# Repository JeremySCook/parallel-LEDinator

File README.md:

# parallel-LEDinator
LED indicators for DB25 parallel connections

Video: https://www.youtube.com/watch?v=P86tV40nX3E

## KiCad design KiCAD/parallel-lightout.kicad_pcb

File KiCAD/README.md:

KiCAD files - newest version as of 5/6/2020

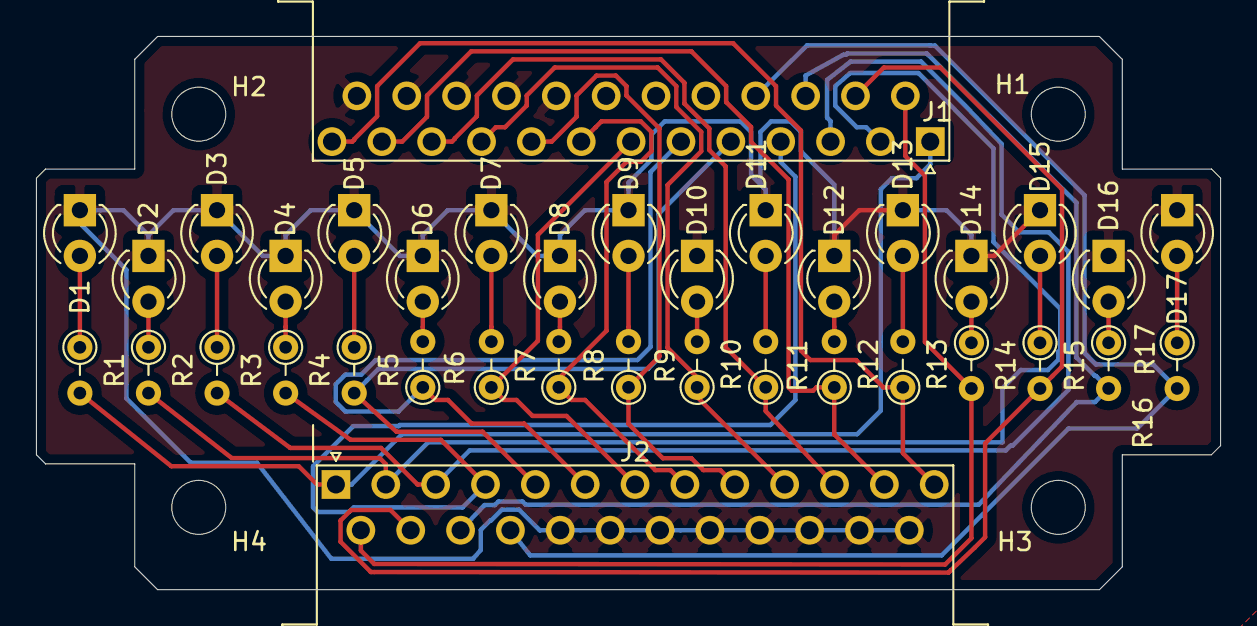
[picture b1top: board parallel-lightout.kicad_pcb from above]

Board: 2 copper layers, 65.8 x 30.7 mm, 40 parts (0 on the bottom side), 35 nets.

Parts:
D1, D2, D3, D4, D5, D6, D7, D8, D9, D10, D11, D12, D13, D14, D15, D16, D17: LED; LED_D3.0mm
H1, H2, H3, H4: MountingHole; MountingHole_3mm
J1, J2: DB25_Male; DSUB-25_Male_Horizontal_P2.77x2.54mm_EdgePinOffset9.40mm
R1, R2, R3, R4, R5, R6, R7, R8, R9, R10, R11, R12, R13, R14, R15, R16, R17: R; R_Axial_DIN0204_L3.6mm_D1.6mm_P2.54mm_Vertical

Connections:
/1: J1.1, J2.1, R1.2
/2: J1.2, J2.2, R2.2
/3: J1.3, J2.3, R3.2
/4: J1.4, J2.4, R4.2
/5: J1.5, J2.5, R5.2
/6: J1.6, J2.6, R6.1
/7: J1.7, J2.7, R7.1
/8: J1.8, J2.8, R8.1
/9: J1.9, J2.9, R9.1
/10: J1.10, J2.10, R10.1
/11: J1.11, J2.11, R11.1
/12: J1.12, J2.12, R12.1
/13: J1.13, J2.13, R13.1
/14: J1.14, J2.14, R14.2
/15: J1.15, J2.15, R15.2
/16: J1.16, J2.16, R16.2
/17: J1.17, J2.17, R17.2
GND: D1.1, D2.1, D3.1, D4.1, D5.1, D6.1, D7.1, D8.1, D9.1, D10.1, D11.1, D12.1, D13.1, D14.1, D15.1, D16.1, D17.1, J1.18, J1.19, J1.20, J1.21, J1.22, J1.23, J1.24, J1.25, J2.18, J2.19, J2.20, J2.21, J2.22, J2.23, J2.24, J2.25
unnamed: D1.2, R1.1
unnamed: D2.2, R2.1
unnamed: D3.2, R3.1
unnamed: D4.2, R4.1
unnamed: D5.2, R5.1
unnamed: D6.2, R6.2
unnamed: D7.2, R7.2
unnamed: D8.2, R8.2
unnamed: D9.2, R9.2
unnamed: D10.2, R10.2
unnamed: D11.2, R11.2
unnamed: D12.2, R12.2
unnamed: D13.2, R13.2
unnamed: D14.2, R14.1
unnamed: D15.2, R15.1
unnamed: D16.2, R16.1
unnamed: D17.2, R17.1
